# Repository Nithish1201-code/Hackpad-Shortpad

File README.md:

# ShortPad

6-key macropad with an OLED display and RGB LEDs built around a Seeed XIAO RP2040. I made this for Hack Club Stardance because I wanted to build my first proper PCB and get some hands-on experience with electronics, CAD, firmware, and basically the whole process of making a hardware project. I also wanted to earn some Stardust, so getting to learn all of this while working toward something useful felt like a pretty good opportunity.

## Overview

ShortPad is my first proper hardware project, and pretty much my first time working with most of the tools involved in building something like this. I designed the PCB in KiCad, made a custom two-piece case in Tinkercad, set up QMK firmware, and added an I2C OLED and addressable RGB LEDs to the basic 6-key macropad design.

The main goal was honestly just to get a feel for the whole process. Before starting this, I had never designed a PCB, made a proper 3D case, or worked with QMK, or anything hardware for that matter. So a lot of the project was learning as I went, figuring things out when they didn't work, and gradually putting all the pieces together.

## Parts List

### Electronics

| Component           | Quantity | Specification               |
| ------------------- | -------: | --------------------------- |
| Seeed XIAO RP2040   |        1 | XIAO RP2040                 |
| OLED Display        |        1 | ER-OLEDM0.91 0.91" I2C OLED |
| Mechanical Switches |        6 | Cherry MX-compatible        |
| Addressable LEDs    |        6 | SK6812MINI-E                |
| Capacitors          |        6 | 100nF, 0603 SMD             |

### Mechanical

| Component        | Quantity | Specification                                |
| ---------------- | -------: | -------------------------------------------- |
| Keycaps          |        6 | MX-compatible DSA keycaps                    |
| Heat-set Inserts |        4 | M3 × 5 × 4 mm                                |
| Screws           |        4 | M3 × 16 mm                                   |
| 3D-printed Case  |        1 | Custom case split into top and bottom pieces |

## PCB Design

The PCB was designed in KiCad, and this was my first time doing a proper PCB from scratch. The board is built around the XIAO RP2040 and includes the six mechanical switches, six SK6812MINI-E RGB LEDs, the OLED interface, and the supporting components needed for the design.

I wanted to keep the board fairly compact while still making sure everything would fit properly inside the case. I also added a 100nF capacitor for each RGB LED and prepared the Gerber files for manufacturing.

## Case Design

The case was designed from scratch in Tinkercad and is split into separate top and bottom pieces. It uses four M3 heat-set inserts and four M3 × 16 mm screws to hold everything together.

I haven't printed the case yet since the project is currently at the design and approval stage but the final STL files are already included in the repository and are ready for printing.

## Firmware

Built using QMK. The firmware source is in `Firmware/hackpad_6key/`, and the compiled `.uf2` file is included in `production/firmware.uf2`.

I'm still fairly new to QMK and haven't gone especially deep into it yet. I used AI to help generate part of the initial firmware since there were some areas I wasn't familiar with, then made my own changes and adjustments to get it working the way I wanted.

I also enabled VIA so the macropad can be configured through software instead of having everything permanently hardcoded. And im currently working on the OLED software as well, with the idea that the display and RGB effects can be configured and expanded over time.

## What I Learned

This project ended up being a pretty good crash course in hardware development. I learned, or am still learning, things like:

| Area                                                                                         | 
| -------------------------------------------------------------------------------------------- | 
| KiCad and PCB design                                                                         | 
| PCB routing                                                                                  | 
| electronics and component selection                                                          | 
| QMK and VIA                                                                                  | 
| I2C and OLED displays                                                                        | 
| addressable RGB LEDs                                                                         | 
| CAD and 3D modelling                                                                         | 
| Tinkercad                                                                                    | 
| 3D printing                                                                                  | 
| Gerber and other production files                                                            | 
| designing around a microcontroller and making the different parts of a project work together | 

I'm definitely not an expert in all of these yet, especially QMK and complited stuff like that, but that was kinda the point. I wanted to actually build something instead of waiting until I knew everything first, and this gave me a reason to learn a lot of new things along the way.

## Why I Built It

I wanted to make my first proper PCB, and a macropad seemed like a good project to start with because it was small enough to be manageable but still involved a lot of different parts of hardware development.

It also gave me an excuse to try things I hadn't worked with before like PCB design, CAD, electronics, firmware, OLEDs, RGB LEDs, and eventually 3D printing. And honestly getting some Stardust out of it was another reason I wanted to give it a shot. I'm also interested in getting some basic tools for future projects, like a soldering iron, so being able to build something I actually wanted while also getting resources to keep experimenting felt like a pretty good win-win.

I started Stardance only a couple of days ago, and this project was basically me wanting to see what I could make from scratch. It was my first PCB, my first real CAD project, and my first time bringing all these different parts together into one design. I mainly wanted to get a feel for the process, learn how everything fits together, and hopefully use what I learned here for more ambitious projects later.

<!-- SCREENSHOT 10: Final overall project render / finished design -->

## Project Structure

| Path                                         | Contents                                  |
| -------------------------------------------- | ----------------------------------------- |
| `CAD/`                                       | `Fully assembled.stp`                     |
| `Firmware/hackpad_6key/`                     | QMK firmware project                      |
| `Firmware/hackpad_6key/keymaps/default/`     | Default keymap                            |
| `Firmware/hackpad_6key/keymaps/via/`         | VIA keymap                                |
| `Firmware/hackpad_6key/keymaps/via/keymap.c` | VIA keymap source                         |
| `Firmware/hackpad_6key/keyboard.json`        | QMK keyboard definition                   |
| `PCB/`                                       | KiCad PCB, project, and schematic files   |
| `production/`                                | STL files, compiled firmware, and Gerbers |
| `.gitattributes`                             | Git attributes                            |
| `.gitignore`                                 | Git ignore rules                          |
| `README.md`                                  | Project documentation                     |

## Current Status

The PCB, schematic, CAD model, firmware build, STL files, and Gerber production files are all finished and pushed to the repository. The physical PCB and case haven't been produced yet, so the next step is getting the project approved and then actually making it IRL.

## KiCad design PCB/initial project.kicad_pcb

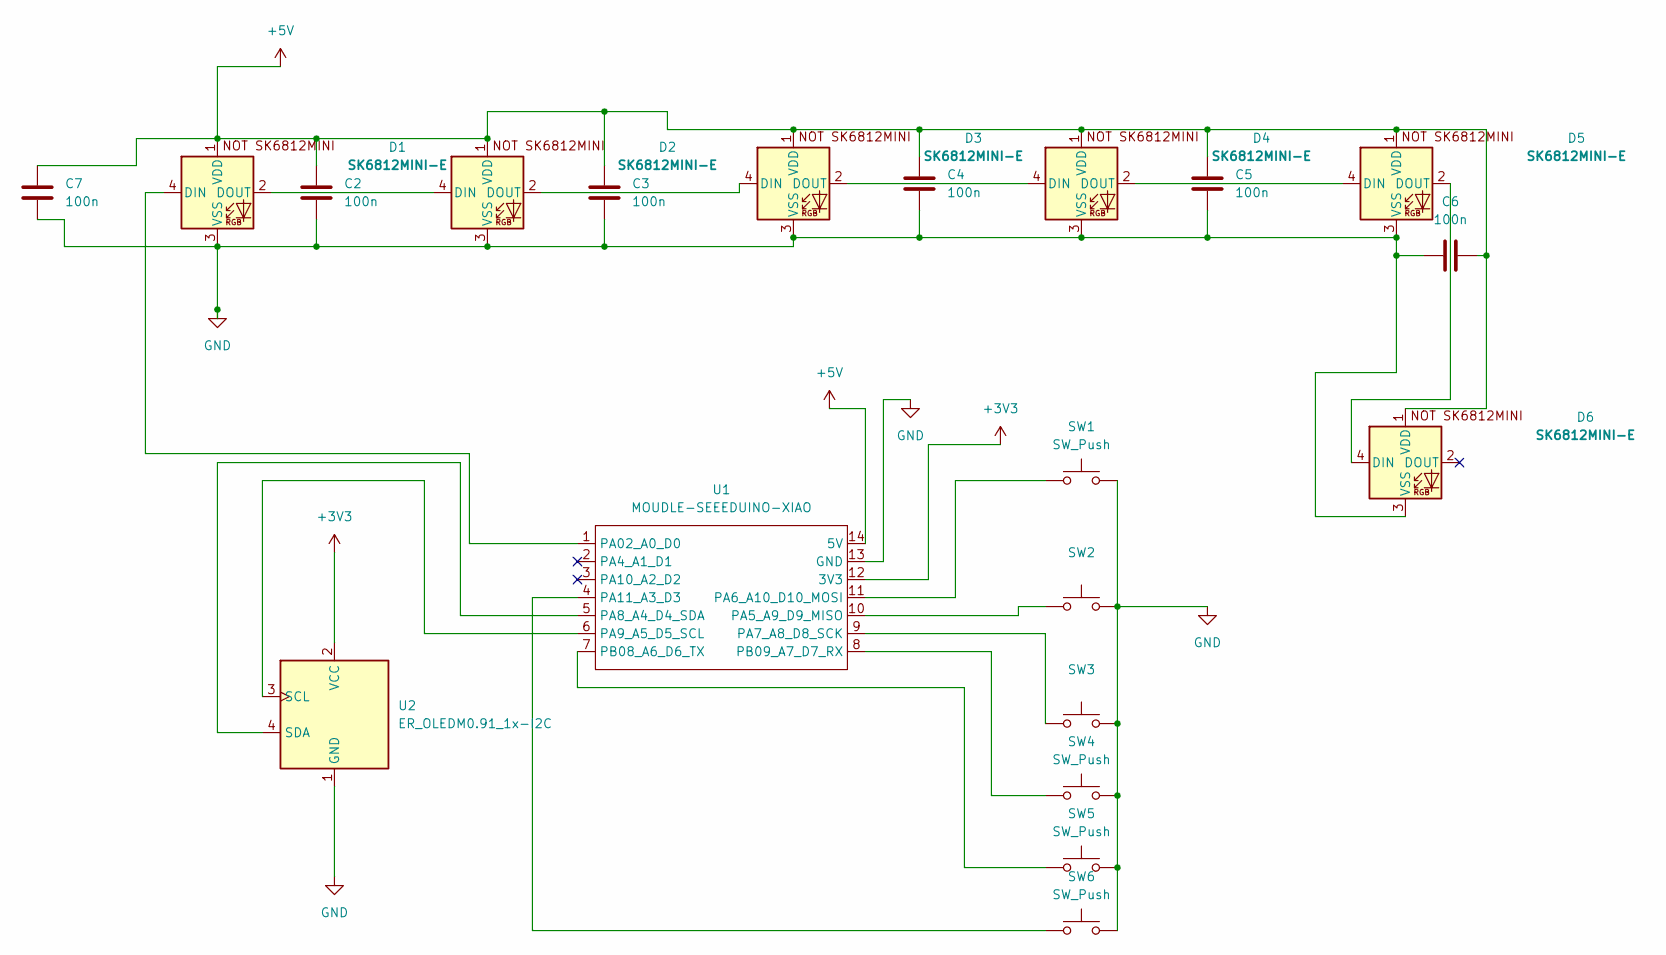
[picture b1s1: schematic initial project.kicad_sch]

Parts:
C2, C3, C4, C5, C6, C7: 100n; C_0603_1608Metric_Pad1.08x0.95mm_HandSolder
D1, D2, D3, D4, D5, D6: SK6812MINI-E; MX_SK6812MINI-E
SW1, SW3, SW4, SW5, SW6: SW_Push; SW_Cherry_MX_PCB_1.00u
SW2: SW_Push; SW_Cherry_MX_PCB
U1: MOUDLE-SEEEDUINO-XIAO; XIAO-Generic-Hybrid-14P-2.54-21X17.8MM
U2: ER_OLEDM0.91_1x-I2C

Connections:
+3V3: U1.12 (3V3), U2.2 (VCC)
+5V: C2.1, C3.1, C4.1, C5.1, C6.1, C7.2, D1.1 (VDD), D2.1 (VDD), D3.1 (VDD), D4.1 (VDD), D5.1 (VDD), D6.1 (VDD), U1.14 (5V)
GND: C2.2, C3.2, C4.2, C5.2, C6.2, C7.1, D1.3 (VSS), D2.3 (VSS), D3.3 (VSS), D4.3 (VSS), D5.3 (VSS), D6.3 (VSS), SW1.2, SW2.2, SW3.2, SW4.2, SW5.2, SW6.2, U1.13 (GND), U2.1 (GND)
unnamed: D1.4 (DIN), U1.1 (PA02_A0_D0)
unnamed: D1.2 (DOUT), D2.4 (DIN)
unnamed: D2.2 (DOUT), D3.4 (DIN)
unnamed: D3.2 (DOUT), D4.4 (DIN)
unnamed: D4.2 (DOUT), D5.4 (DIN)
unnamed: D5.2 (DOUT), D6.4 (DIN)
unnamed: SW2.1, U1.10 (PA5_A9_D9_MISO)
unnamed: SW1.1, U1.11 (PA6_A10_D10_MOSI)
unnamed: SW3.1, U1.9 (PA7_A8_D8_SCK)
unnamed: U1.5 (PA8_A4_D4_SDA), U2.4 (SDA)
unnamed: U1.6 (PA9_A5_D5_SCL), U2.3 (SCL)
unnamed: SW6.1, U1.4 (PA11_A3_D3)
unnamed: SW5.1, U1.7 (PB08_A6_D6_TX)
unnamed: SW4.1, U1.8 (PB09_A7_D7_RX)

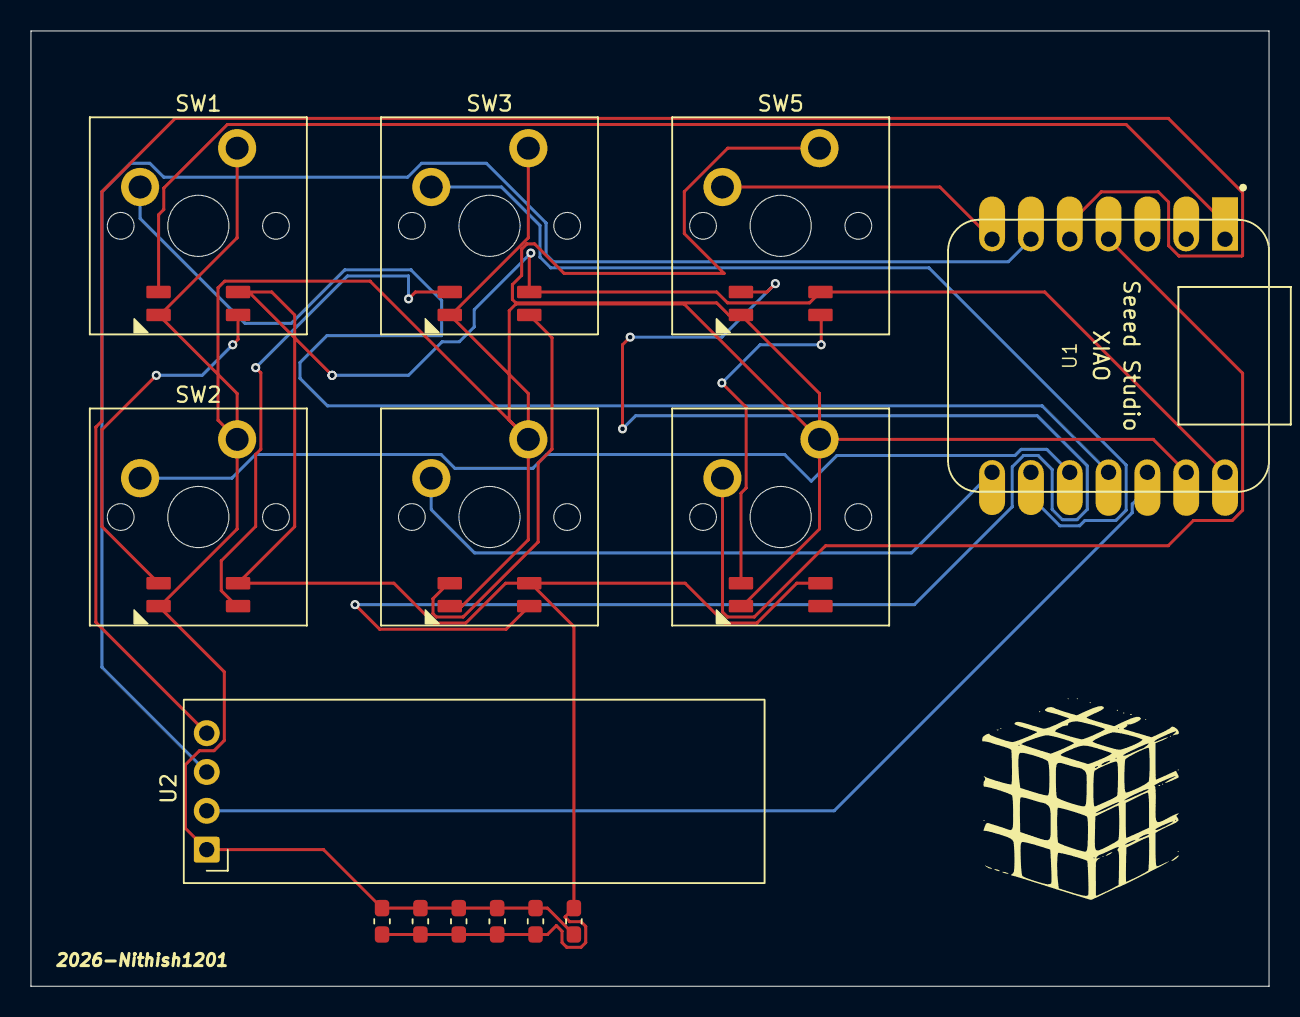
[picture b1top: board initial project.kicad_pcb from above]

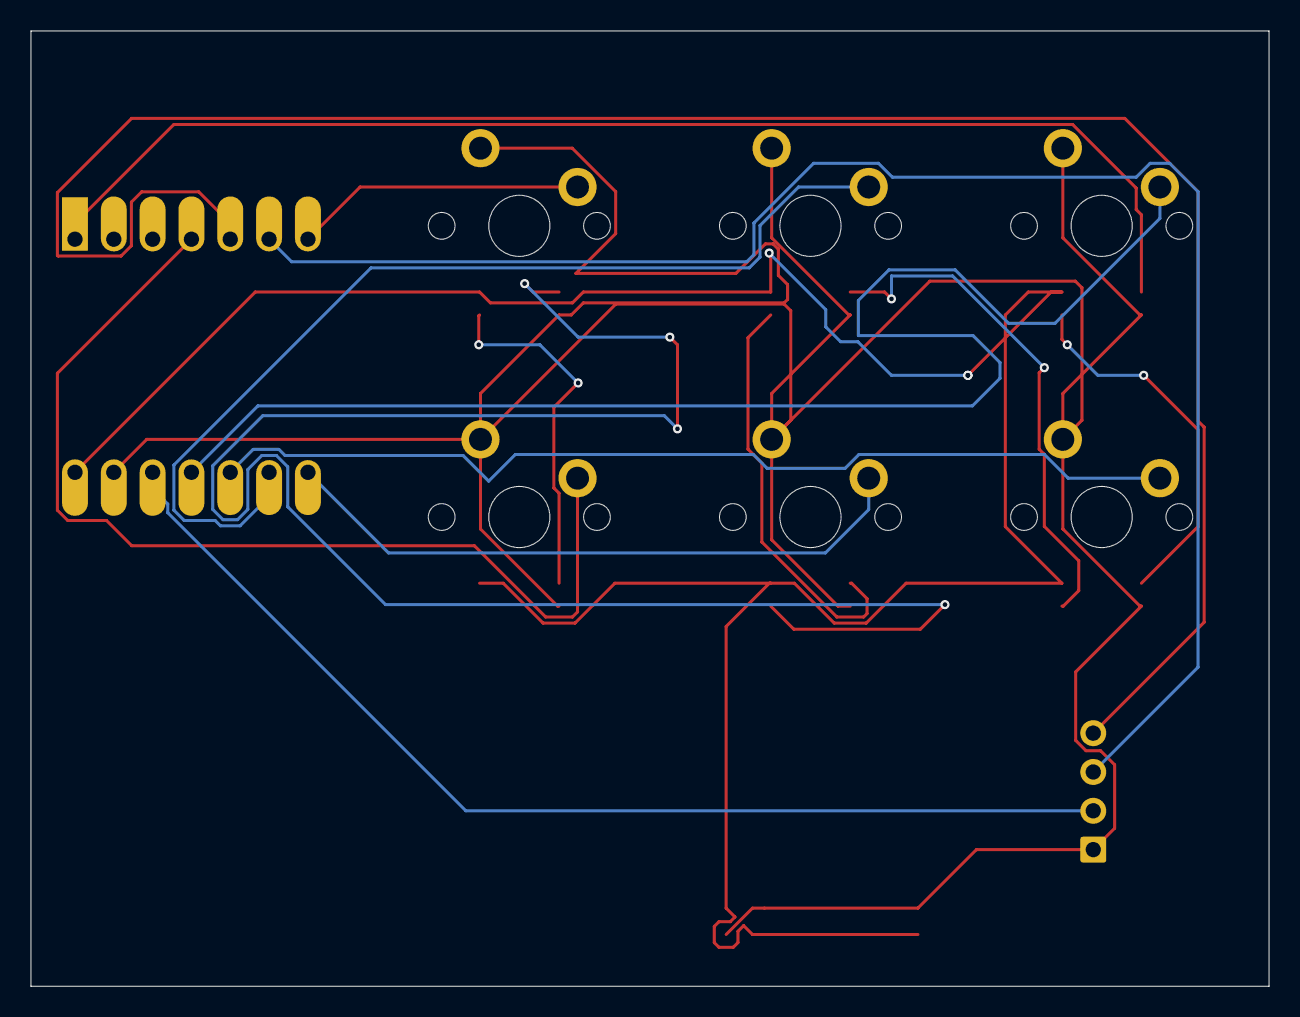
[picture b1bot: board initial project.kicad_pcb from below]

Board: 2 copper layers, 81.0 x 62.5 mm, 20 parts (6 on the bottom side), 17 nets.
